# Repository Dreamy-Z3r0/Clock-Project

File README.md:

# Clock project
Final product is a digital wallclock that makes use of an STM32 Blue Pill as main microcontroller and a generic ESP8266 as gateway for remote access.

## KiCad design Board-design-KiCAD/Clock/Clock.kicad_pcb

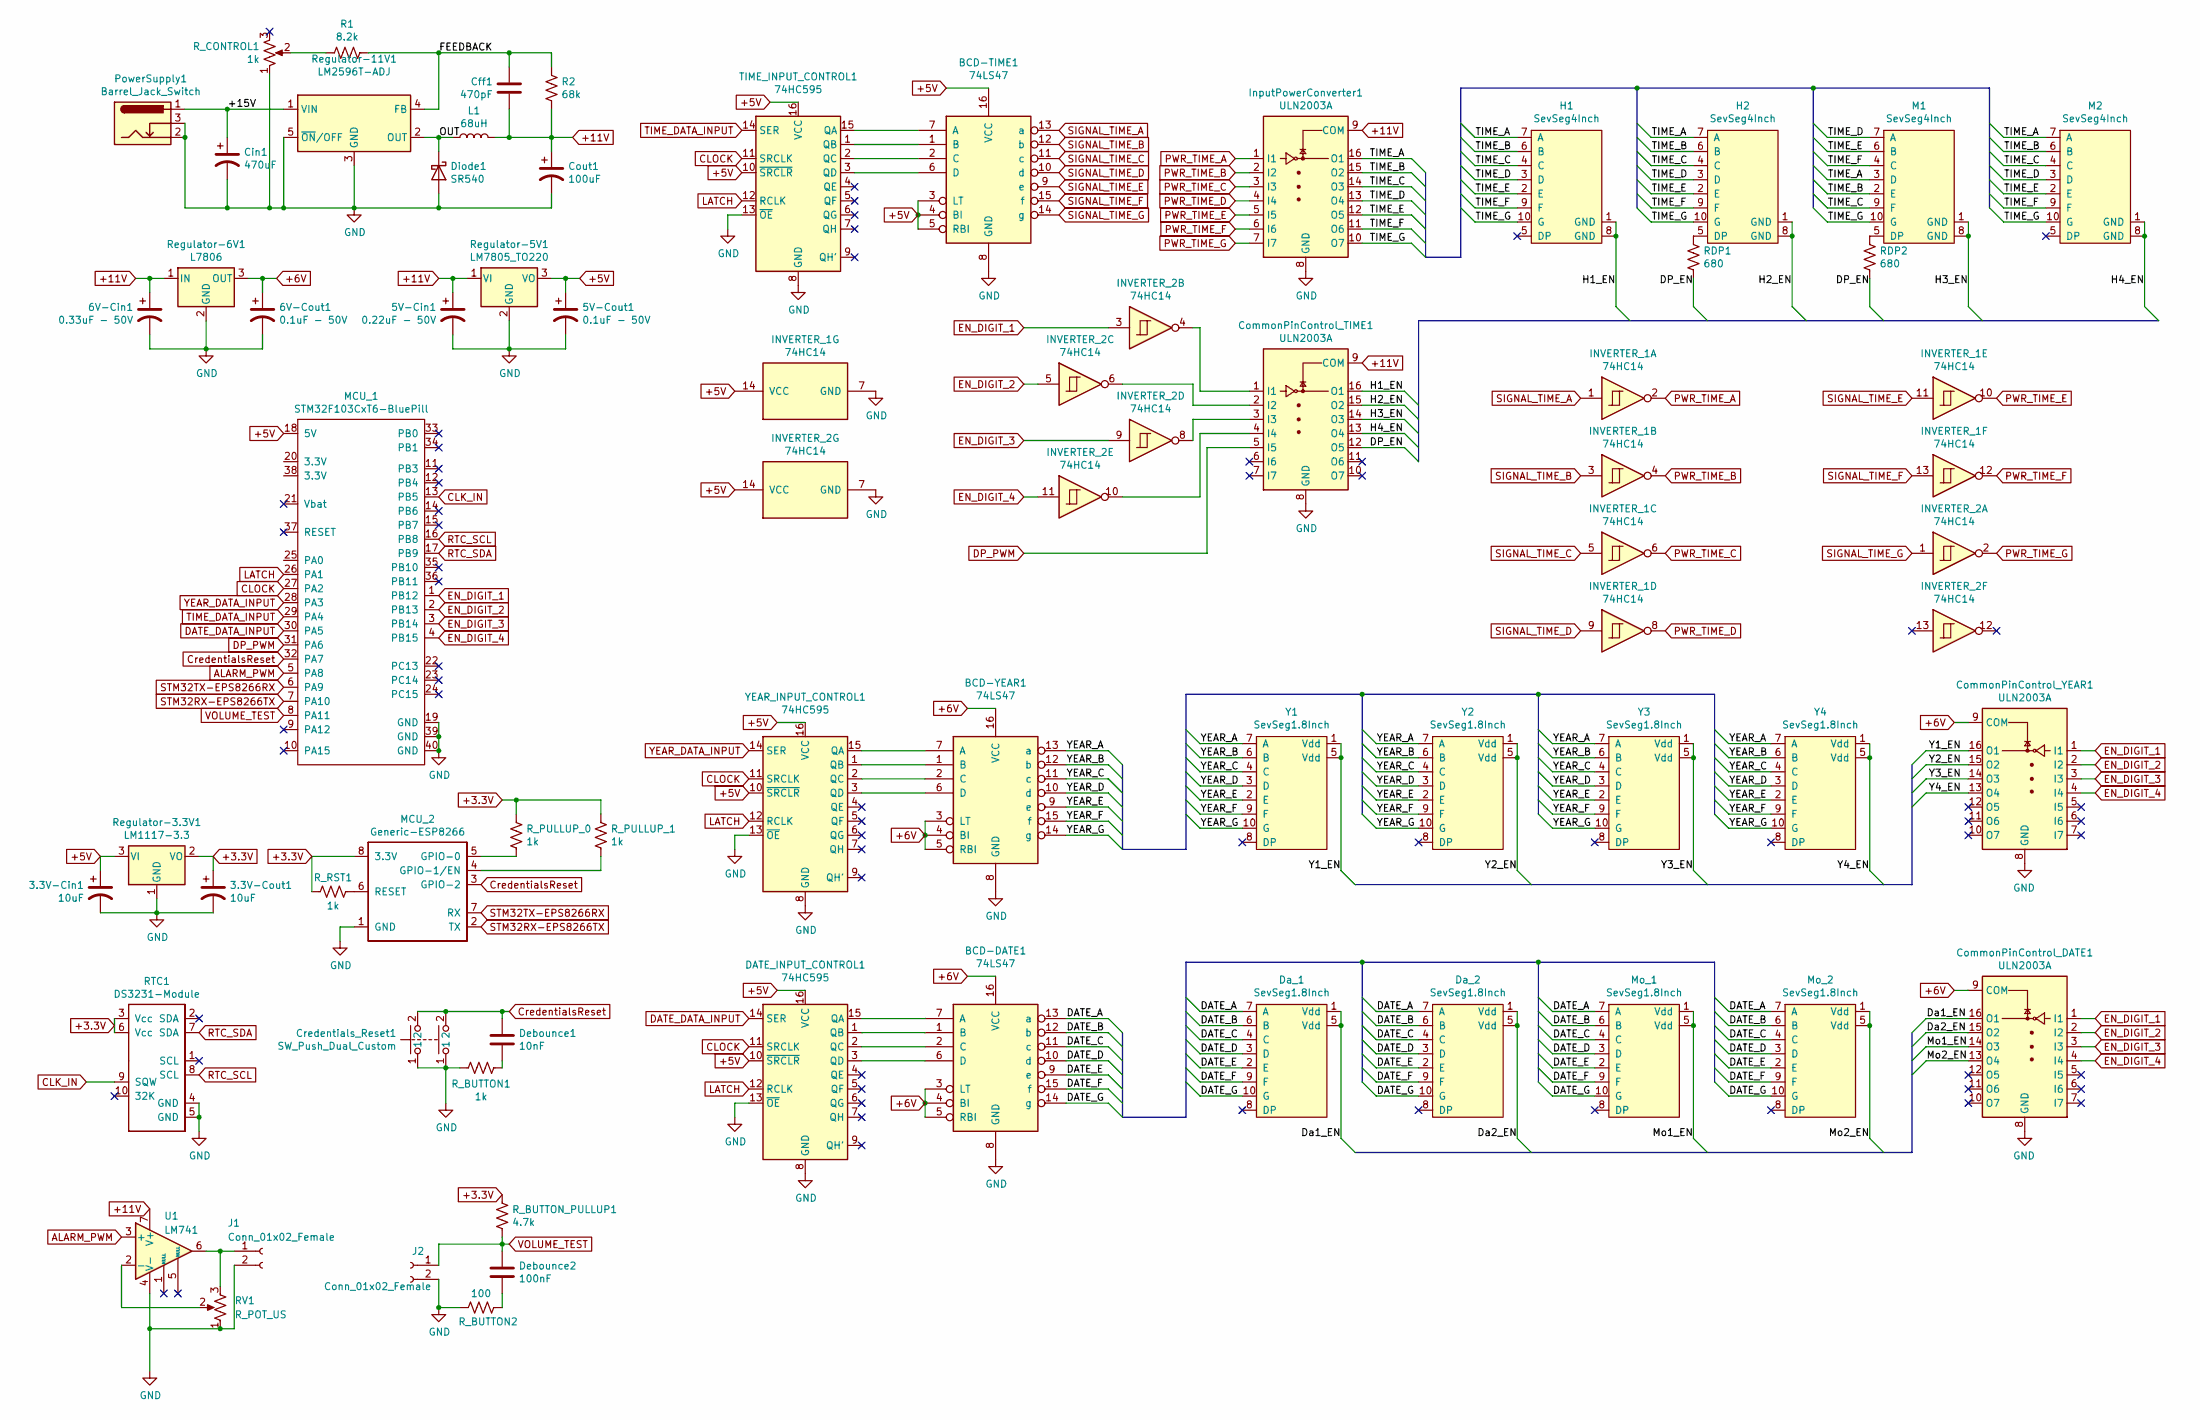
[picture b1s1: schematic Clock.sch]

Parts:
3.3V-Cin1, 3.3V-Cout1: 10uF; CP_Radial_D4.0mm_P2.00mm
5V-Cin1: 0.22uF - 50V; CP_Radial_D4.0mm_P2.00mm
5V-Cout1, 6V-Cout1: 0.1uF - 50V; CP_Radial_D5.0mm_P2.00mm
6V-Cin1: 0.33uF - 50V; CP_Radial_D4.0mm_P2.00mm
BCD-DATE1: 74LS47; DIP-16_W7.62mm_Socket_LongPads
BCD-TIME1: 74LS47; DIP-16_W7.62mm_Socket_LongPads
BCD-YEAR1: 74LS47; DIP-16_W7.62mm_Socket_LongPads
Cff1: 470pF; CP_Radial_H15.0mm_W14.0mm_T8.0mm_P8.5mm_Horizontal
Cin1: 470uF; CP_Radial_D10.0mm_P5.00mm
CommonPinControl_DATE1: ULN2003A; DIP-16_W7.62mm_Socket_LongPads
CommonPinControl_TIME1: ULN2003A; DIP-16_W7.62mm_Socket_LongPads
CommonPinControl_YEAR1: ULN2003A; DIP-16_W7.62mm_Socket_LongPads
Cout1: 100uF; CP_Radial_D8.0mm_P3.50mm
Credentials_Reset1: SW_Push_Dual_Custom; SW_PUSH-12mm_Wuerth-430476085716
DATE_INPUT_CONTROL1: 74HC595; DIP-16_W7.62mm_Socket_LongPads
Da_1, Da_2: SevSeg1.8Inch
Debounce1: 10nF; CP_Radial_H15.0mm_W14.0mm_T8.0mm_P8.5mm_Horizontal
Debounce2: 100nF; CP_Radial_H15.0mm_W14.0mm_T8.0mm_P8.5mm_Horizontal
Diode1: SR540; D_5600_9500Metric
H1, H2: SevSeg4Inch; SevSeg4inch
INVERTER_1, INVERTER_2: 74HC14; DIP-14_W7.62mm_Socket_LongPads
InputPowerConverter1: ULN2003A; DIP-16_W7.62mm_Socket_LongPads
J1, J2: Conn_01x02_Female; PinHeader_1x02_P2.54mm_Vertical
L1: 68uH; L_Radial_D10.0mm_P5.5mm
M1, M2: SevSeg4Inch; SevSeg4inch
MCU_1: STM32F103CxT6-BluePill
MCU_2: Generic-ESP8266
Mo_1, Mo_2: SevSeg1.8Inch
PowerSupply1: Barrel_Jack_Switch; BarrelJack_Horizontal
R1: 8.2k; R_Axial_DIN0207_L6.3mm_D2.5mm_P10.16mm_Horizontal
R2: 68k; R_Axial_DIN0207_L6.3mm_D2.5mm_P10.16mm_Horizontal
RDP1, RDP2: 680; R_Axial_DIN0207_L6.3mm_D2.5mm_P10.16mm_Horizontal
RTC1: DS3231-Module
RV1: R_POT_US; Potentiometer_Piher_T-16H_Single_Horizontal
R_BUTTON1: 1k; R_Axial_DIN0207_L6.3mm_D2.5mm_P10.16mm_Horizontal
R_BUTTON2: 100; R_Axial_DIN0207_L6.3mm_D2.5mm_P10.16mm_Horizontal
R_BUTTON_PULLUP1: 4.7k; R_Axial_DIN0207_L6.3mm_D2.5mm_P10.16mm_Horizontal
R_CONTROL1: 1k; Potentiometer_Vishay_T73YP_Vertical
R_PULLUP_0, R_PULLUP_1: 1k; R_Axial_DIN0207_L6.3mm_D2.5mm_P10.16mm_Horizontal
R_RST1: 1k; R_Axial_DIN0207_L6.3mm_D2.5mm_P10.16mm_Horizontal
Regulator-3.3V1: LM1117-3.3; TO-220-3_Horizontal_TabDown
Regulator-5V1: LM7805_TO220; TO-220-3_Horizontal_TabDown
Regulator-6V1: L7806; TO-220-3_Horizontal_TabDown
Regulator-11V1: LM2596T-ADJ; TO-220-5_Horizontal_TabUp
TIME_INPUT_CONTROL1: 74HC595; DIP-16_W7.62mm_Socket_LongPads
U1: LM741; DIP-8_W7.62mm_Socket_LongPads
Y1, Y2, Y3, Y4: SevSeg1.8Inch
YEAR_INPUT_CONTROL1: 74HC595; DIP-16_W7.62mm_Socket_LongPads

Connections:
+3.3V: 3.3V-Cout1.1, MCU_2.8 (3.3V), RTC1.3 (Vcc), RTC1.6 (Vcc), R_BUTTON_PULLUP1.1, R_PULLUP_0.1, R_PULLUP_1.1, R_RST1.2, Regulator-3.3V1.2 (VO)
+5V: 3.3V-Cin1.1, 5V-Cout1.1, BCD-TIME1.3 (LT), BCD-TIME1.4 (BI), BCD-TIME1.5 (RBI), BCD-TIME1.16 (VCC), DATE_INPUT_CONTROL1.10 (~SRCLR), DATE_INPUT_CONTROL1.16 (VCC), INVERTER_1.14 (VCC), INVERTER_2.14 (VCC), MCU_1.18 (5V), Regulator-3.3V1.3 (VI), Regulator-5V1.3 (VO), TIME_INPUT_CONTROL1.10 (~SRCLR), TIME_INPUT_CONTROL1.16 (VCC), YEAR_INPUT_CONTROL1.10 (~SRCLR), YEAR_INPUT_CONTROL1.16 (VCC)
+6V: 6V-Cout1.1, BCD-DATE1.3 (LT), BCD-DATE1.4 (BI), BCD-DATE1.5 (RBI), BCD-DATE1.16 (VCC), BCD-YEAR1.3 (LT), BCD-YEAR1.4 (BI), BCD-YEAR1.5 (RBI), BCD-YEAR1.16 (VCC), CommonPinControl_DATE1.9 (COM), CommonPinControl_YEAR1.9 (COM), Regulator-6V1.3 (OUT)
+11V: 5V-Cin1.1, 6V-Cin1.1, Cff1.2, CommonPinControl_TIME1.9 (COM), Cout1.1, InputPowerConverter1.9 (COM), L1.2, R2.2, Regulator-5V1.1 (VI), Regulator-6V1.1 (IN), U1.7 (V+)
/+15V: Cin1.1, PowerSupply1.1, Regulator-11V1.1 (VIN)
/DATE_A: BCD-DATE1.13 (a), Da_1.7 (A), Da_2.7 (A), Mo_1.7 (A), Mo_2.7 (A)
/DATE_B: BCD-DATE1.12 (b), Da_1.6 (B), Da_2.6 (B), Mo_1.6 (B), Mo_2.6 (B)
/DATE_C: BCD-DATE1.11 (c), Da_1.4 (C), Da_2.4 (C), Mo_1.4 (C), Mo_2.4 (C)
/DATE_D: BCD-DATE1.10 (d), Da_1.3 (D), Da_2.3 (D), Mo_1.3 (D), Mo_2.3 (D)
/DATE_E: BCD-DATE1.9 (e), Da_1.2 (E), Da_2.2 (E), Mo_1.2 (E), Mo_2.2 (E)
/DATE_F: BCD-DATE1.15 (f), Da_1.9 (F), Da_2.9 (F), Mo_1.9 (F), Mo_2.9 (F)
/DATE_G: BCD-DATE1.14 (g), Da_1.10 (G), Da_2.10 (G), Mo_1.10 (G), Mo_2.10 (G)
/DP_EN: CommonPinControl_TIME1.12 (O5), RDP1.2, RDP2.2
/Da1_EN: CommonPinControl_DATE1.16 (O1), Da_1.1 (Vdd), Da_1.5 (Vdd)
/Da2_EN: CommonPinControl_DATE1.15 (O2), Da_2.1 (Vdd), Da_2.5 (Vdd)
/FEEDBACK: Cff1.1, R1.2, R2.1, Regulator-11V1.4 (FB)
/H1_EN: CommonPinControl_TIME1.16 (O1), H1.1 (GND), H1.8 (GND)
/H2_EN: CommonPinControl_TIME1.15 (O2), H2.1 (GND), H2.8 (GND)
/H3_EN: CommonPinControl_TIME1.14 (O3), M1.1 (GND), M1.8 (GND)
/H4_EN: CommonPinControl_TIME1.13 (O4), M2.1 (GND), M2.8 (GND)
/Mo1_EN: CommonPinControl_DATE1.14 (O3), Mo_1.1 (Vdd), Mo_1.5 (Vdd)
/Mo2_EN: CommonPinControl_DATE1.13 (O4), Mo_2.1 (Vdd), Mo_2.5 (Vdd)
/OUT: Diode1.1 (K), L1.1, Regulator-11V1.2 (OUT)
/TIME_A: H1.7 (A), H2.7 (A), InputPowerConverter1.16 (O1), M1.3 (D), M2.7 (A)
/TIME_B: H1.6 (B), H2.6 (B), InputPowerConverter1.15 (O2), M1.2 (E), M2.6 (B)
/TIME_C: H1.4 (C), H2.4 (C), InputPowerConverter1.14 (O3), M1.9 (F), M2.4 (C)
/TIME_D: H1.3 (D), H2.3 (D), InputPowerConverter1.13 (O4), M1.7 (A), M2.3 (D)
/TIME_E: H1.2 (E), H2.2 (E), InputPowerConverter1.12 (O5), M1.6 (B), M2.2 (E)
/TIME_F: H1.9 (F), H2.9 (F), InputPowerConverter1.11 (O6), M1.4 (C), M2.9 (F)
/TIME_G: H1.10 (G), H2.10 (G), InputPowerConverter1.10 (O7), M1.10 (G), M2.10 (G)
/Y1_EN: CommonPinControl_YEAR1.16 (O1), Y1.1 (Vdd), Y1.5 (Vdd)
/Y2_EN: CommonPinControl_YEAR1.15 (O2), Y2.1 (Vdd), Y2.5 (Vdd)
/Y3_EN: CommonPinControl_YEAR1.14 (O3), Y3.1 (Vdd), Y3.5 (Vdd)
/Y4_EN: CommonPinControl_YEAR1.13 (O4), Y4.1 (Vdd), Y4.5 (Vdd)
/YEAR_A: BCD-YEAR1.13 (a), Y1.7 (A), Y2.7 (A), Y3.7 (A), Y4.7 (A)
/YEAR_B: BCD-YEAR1.12 (b), Y1.6 (B), Y2.6 (B), Y3.6 (B), Y4.6 (B)
/YEAR_C: BCD-YEAR1.11 (c), Y1.4 (C), Y2.4 (C), Y3.4 (C), Y4.4 (C)
/YEAR_D: BCD-YEAR1.10 (d), Y1.3 (D), Y2.3 (D), Y3.3 (D), Y4.3 (D)
/YEAR_E: BCD-YEAR1.9 (e), Y1.2 (E), Y2.2 (E), Y3.2 (E), Y4.2 (E)
/YEAR_F: BCD-YEAR1.15 (f), Y1.9 (F), Y2.9 (F), Y3.9 (F), Y4.9 (F)
/YEAR_G: BCD-YEAR1.14 (g), Y1.10 (G), Y2.10 (G), Y3.10 (G), Y4.10 (G)
ALARM_PWM: MCU_1.5 (PA8), U1.3 (+)
CLK_IN: MCU_1.13 (PB5), RTC1.9 (SQW)
CLOCK: DATE_INPUT_CONTROL1.11 (SRCLK), MCU_1.27 (PA2), TIME_INPUT_CONTROL1.11 (SRCLK), YEAR_INPUT_CONTROL1.11 (SRCLK)
CredentialsReset: Credentials_Reset1.2, Debounce1.1, MCU_1.32 (PA7), MCU_2.3 (GPIO-2)
DATE_DATA_INPUT: DATE_INPUT_CONTROL1.14 (SER), MCU_1.30 (PA5)
DP_PWM: CommonPinControl_TIME1.5 (I5), MCU_1.31 (PA6)
EN_DIGIT_1: CommonPinControl_DATE1.1 (I1), CommonPinControl_YEAR1.1 (I1), INVERTER_2.3, MCU_1.1 (PB12)
EN_DIGIT_2: CommonPinControl_DATE1.2 (I2), CommonPinControl_YEAR1.2 (I2), INVERTER_2.5, MCU_1.2 (PB13)
EN_DIGIT_3: CommonPinControl_DATE1.3 (I3), CommonPinControl_YEAR1.3 (I3), INVERTER_2.9, MCU_1.3 (PB14)
EN_DIGIT_4: CommonPinControl_DATE1.4 (I4), CommonPinControl_YEAR1.4 (I4), INVERTER_2.11, MCU_1.4 (PB15)
GND: 3.3V-Cin1.2, 3.3V-Cout1.2, 5V-Cin1.2, 5V-Cout1.2, 6V-Cin1.2, 6V-Cout1.2, BCD-DATE1.8 (GND), BCD-TIME1.8 (GND), BCD-YEAR1.8 (GND), Cin1.2, CommonPinControl_DATE1.8 (GND), CommonPinControl_TIME1.8 (GND), CommonPinControl_YEAR1.8 (GND), Cout1.2, Credentials_Reset1.1, DATE_INPUT_CONTROL1.8 (GND), DATE_INPUT_CONTROL1.13 (~OE), Diode1.2 (A), INVERTER_1.7 (GND), INVERTER_2.7 (GND), InputPowerConverter1.8 (GND), J1.2, J2.2, MCU_1.19 (GND), MCU_1.39 (GND), MCU_1.40 (GND), MCU_2.1 (GND), PowerSupply1.2, PowerSupply1.3, RTC1.4 (GND), RTC1.5 (GND), RV1.1, R_BUTTON1.1, R_BUTTON2.2, R_CONTROL1.1, Regulator-3.3V1.1 (GND), Regulator-5V1.2 (GND), Regulator-6V1.2 (GND), Regulator-11V1.3 (GND), Regulator-11V1.5 (~ON~/OFF), TIME_INPUT_CONTROL1.8 (GND), TIME_INPUT_CONTROL1.13 (~OE), U1.4 (V-), YEAR_INPUT_CONTROL1.8 (GND), YEAR_INPUT_CONTROL1.13 (~OE)
LATCH: DATE_INPUT_CONTROL1.12 (RCLK), MCU_1.26 (PA1), TIME_INPUT_CONTROL1.12 (RCLK), YEAR_INPUT_CONTROL1.12 (RCLK)
unnamed: BCD-DATE1.1 (B), DATE_INPUT_CONTROL1.1 (QB)
unnamed: BCD-DATE1.2 (C), DATE_INPUT_CONTROL1.2 (QC)
unnamed: BCD-DATE1.6 (D), DATE_INPUT_CONTROL1.3 (QD)
unnamed: BCD-DATE1.7 (A), DATE_INPUT_CONTROL1.15 (QA)
unnamed: BCD-TIME1.1 (B), TIME_INPUT_CONTROL1.1 (QB)
unnamed: BCD-TIME1.2 (C), TIME_INPUT_CONTROL1.2 (QC)
unnamed: BCD-TIME1.6 (D), TIME_INPUT_CONTROL1.3 (QD)
unnamed: BCD-TIME1.7 (A), TIME_INPUT_CONTROL1.15 (QA)
unnamed: BCD-YEAR1.1 (B), YEAR_INPUT_CONTROL1.1 (QB)
unnamed: BCD-YEAR1.2 (C), YEAR_INPUT_CONTROL1.2 (QC)
unnamed: BCD-YEAR1.6 (D), YEAR_INPUT_CONTROL1.3 (QD)
unnamed: BCD-YEAR1.7 (A), YEAR_INPUT_CONTROL1.15 (QA)
unnamed: CommonPinControl_TIME1.1 (I1), INVERTER_2.4
unnamed: CommonPinControl_TIME1.2 (I2), INVERTER_2.6
unnamed: CommonPinControl_TIME1.3 (I3), INVERTER_2.8
unnamed: CommonPinControl_TIME1.4 (I4), INVERTER_2.10
unnamed: Debounce1.2, R_BUTTON1.2
unnamed: Debounce2.2, R_BUTTON2.1
unnamed: H2.5 (DP), RDP1.1
unnamed: J1.1, RV1.3, U1.6
unnamed: M1.5 (DP), RDP2.1
unnamed: MCU_2.4 (GPIO-1/EN), R_PULLUP_1.2
unnamed: MCU_2.5 (GPIO-0), R_PULLUP_0.2
unnamed: MCU_2.6 (RESET), R_RST1.1
unnamed: R1.1, R_CONTROL1.2
unnamed: RV1.2, U1.2 (-)
PWR_TIME_A: INVERTER_1.2, InputPowerConverter1.1 (I1)
PWR_TIME_B: INVERTER_1.4, InputPowerConverter1.2 (I2)
PWR_TIME_C: INVERTER_1.6, InputPowerConverter1.3 (I3)
PWR_TIME_D: INVERTER_1.8, InputPowerConverter1.4 (I4)
PWR_TIME_E: INVERTER_1.10, InputPowerConverter1.5 (I5)
PWR_TIME_F: INVERTER_1.12, InputPowerConverter1.6 (I6)
PWR_TIME_G: INVERTER_2.2, InputPowerConverter1.7 (I7)
RTC_SCL: MCU_1.16 (PB8), RTC1.8 (SCL)
RTC_SDA: MCU_1.17 (PB9), RTC1.7 (SDA)
SIGNAL_TIME_A: BCD-TIME1.13 (a), INVERTER_1.1
SIGNAL_TIME_B: BCD-TIME1.12 (b), INVERTER_1.3
SIGNAL_TIME_C: BCD-TIME1.11 (c), INVERTER_1.5
SIGNAL_TIME_D: BCD-TIME1.10 (d), INVERTER_1.9
SIGNAL_TIME_E: BCD-TIME1.9 (e), INVERTER_1.11
SIGNAL_TIME_F: BCD-TIME1.15 (f), INVERTER_1.13
SIGNAL_TIME_G: BCD-TIME1.14 (g), INVERTER_2.1
STM32RX-EPS8266TX: MCU_1.7 (PA10), MCU_2.2 (TX)
STM32TX-EPS8266RX: MCU_1.6 (PA9), MCU_2.7 (RX)
TIME_DATA_INPUT: MCU_1.29 (PA4), TIME_INPUT_CONTROL1.14 (SER)
VOLUME_TEST: Debounce2.1, J2.1, MCU_1.8 (PA11), R_BUTTON_PULLUP1.2
YEAR_DATA_INPUT: MCU_1.28 (PA3), YEAR_INPUT_CONTROL1.14 (SER)

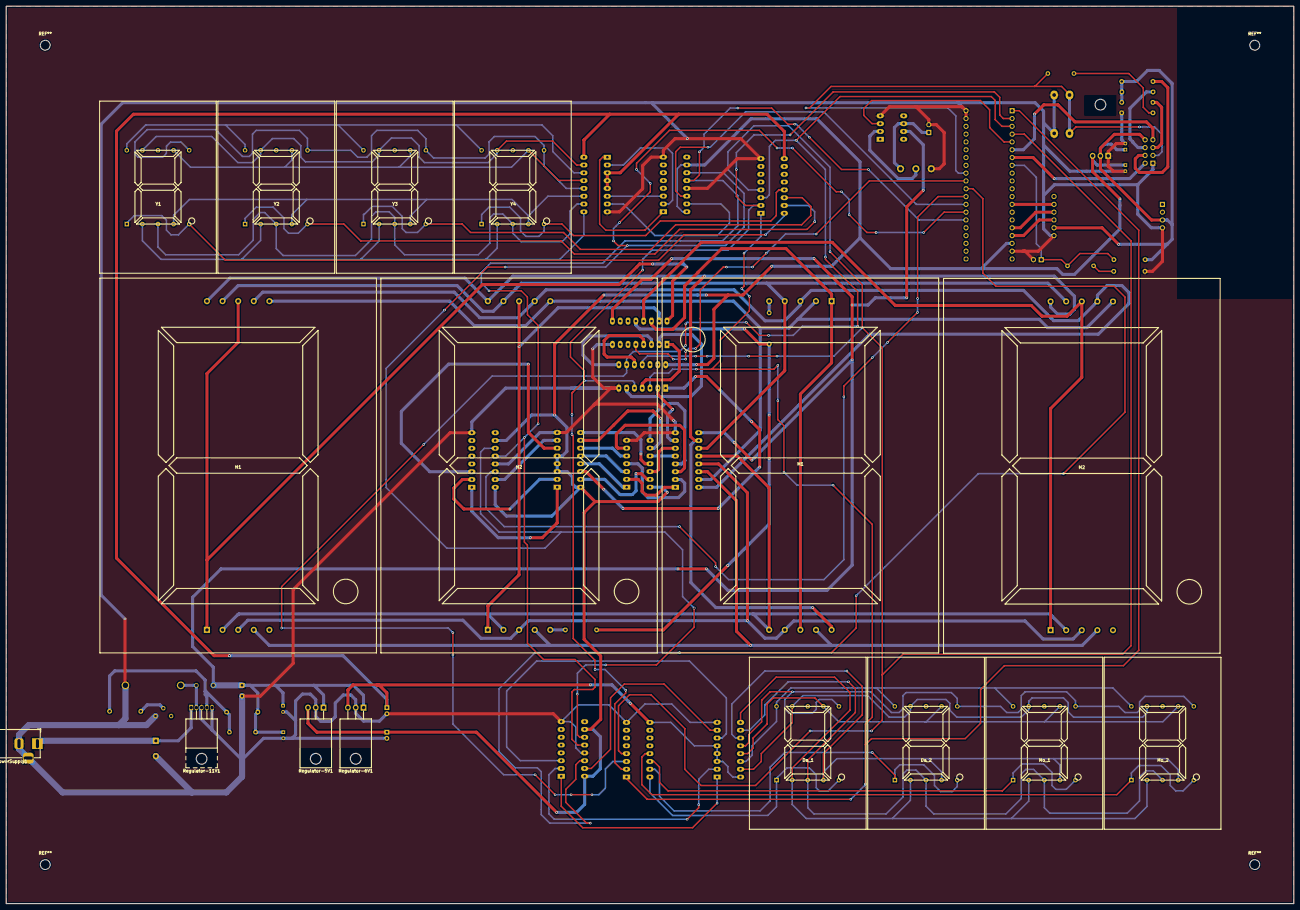
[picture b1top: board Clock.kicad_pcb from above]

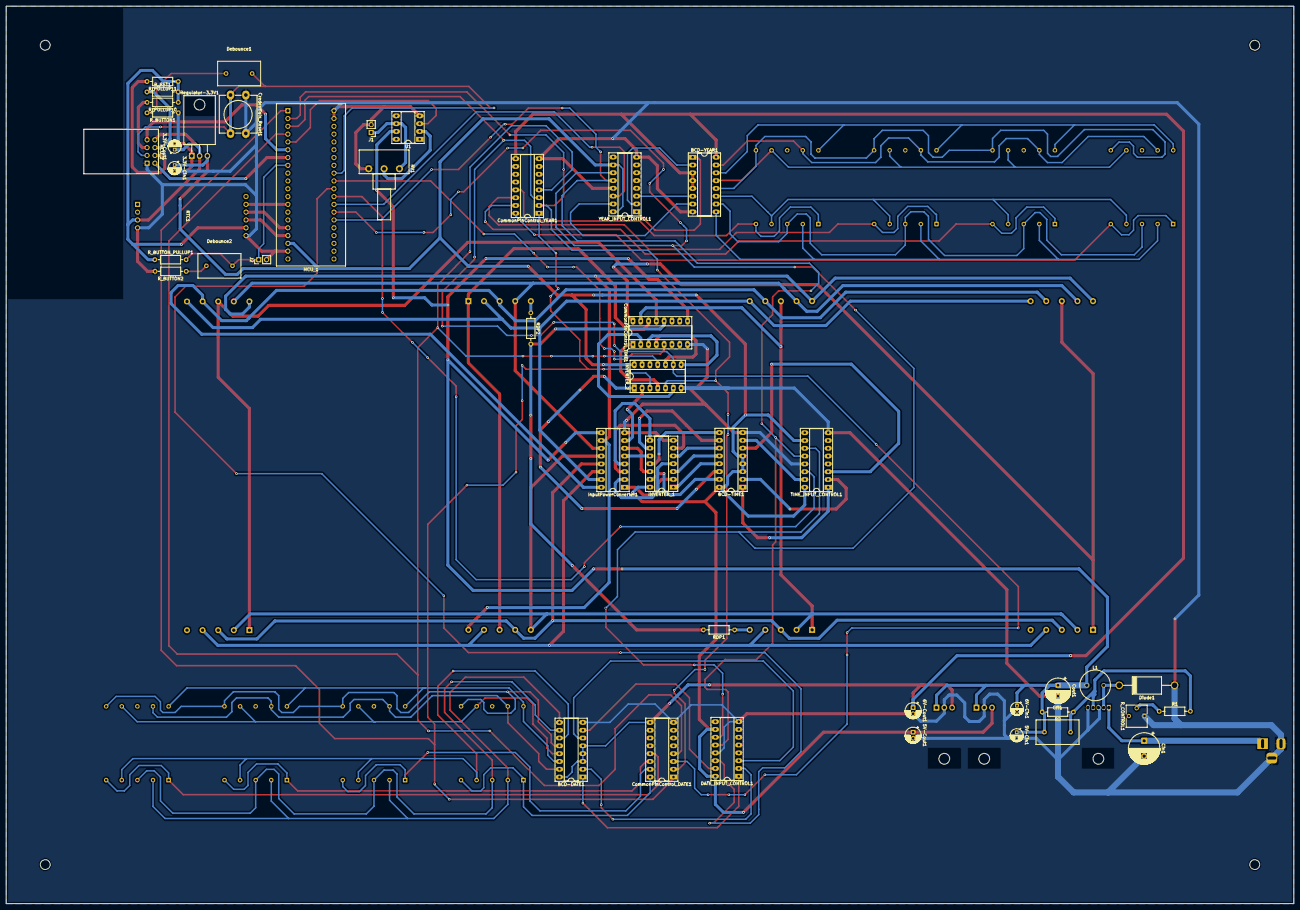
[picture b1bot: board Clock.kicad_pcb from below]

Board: 2 copper layers, 419.1 x 292.1 mm, 61 parts (45 on the bottom side), 100 nets.

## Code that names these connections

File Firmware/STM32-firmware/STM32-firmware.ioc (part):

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PB13.GPIOParameters=GPIO_Speed,GPIO_Label
Mcu.UserName=STM32F103CBTx
PB14.GPIO_Label=EN_DIGIT_3
PC13-TAMPER-RTC.GPIOParameters=GPIO_Label
PA2.GPIO_Speed=GPIO_SPEED_FREQ_HIGH
PA11.GPIOParameters=GPIO_PuPd,GPIO_Label,GPIO_ModeDefaultEXTI
PA3.GPIOParameters=GPIO_Speed,GPIO_Label
PA6.GPIO_Label=DP_OUT
PA11.GPIO_PuPd=GPIO_PULLUP
PB13.GPIO_Label=EN_DIGIT_2
PA3.GPIO_Speed=GPIO_SPEED_FREQ_HIGH
PB13.Signal=GPIO_Output
PB15.Signal=GPIO_Output
PA2.GPIOParameters=GPIO_Speed,GPIO_Label
RCC.SYSCLKSource=RCC_SYSCLKSOURCE_PLLCLK
PB5.GPIOParameters=GPIO_Label,GPIO_ModeDefaultEXTI
PD1-OSC_OUT.Signal=RCC_OSC_OUT
PA8.GPIOParameters=GPIO_Label
PA4.GPIO_Speed=GPIO_SPEED_FREQ_HIGH
PB12.GPIO_Label=EN_DIGIT_1
PA1.GPIOParameters=GPIO_Speed,PinState,GPIO_Label
PA14.Mode=Serial_Wire
PA8.Signal=GPIO_Output
PB9.Signal=I2C1_SDA
Mcu.Package=LQFP48
PA6.Signal=GPIO_Output
PA2.GPIO_Label=CLOCK
PA10.Signal=USART1_RX
PA5.GPIOParameters=GPIO_Speed,GPIO_Label
PA1.PinState=GPIO_PIN_RESET
PB14.GPIOParameters=GPIO_Speed,GPIO_Label
PB5.GPIO_Label=CLK_IN
PA4.GPIO_Label=TIME
PA3.Signal=GPIO_Output
PB5.GPIO_ModeDefaultEXTI=GPIO_MODE_IT_RISING
PA6.GPIOParameters=GPIO_Label
PD1-OSC_OUT.Mode=HSE-External-Oscillator
PA10.Mode=Asynchronous
PA7.GPIO_ModeDefaultEXTI=GPIO_MODE_IT_FALLING
PC13-TAMPER-RTC.Signal=GPIO_Output
PA11.GPIO_Label=VOLUME_TEST
PD0-OSC_IN.Signal=RCC_OSC_IN
PA13.Signal=SYS_JTMS-SWDIO
PA9.Mode=Asynchronous
PA8.GPIO_Label=ALARM_PWM
PB14.GPIO_Speed=GPIO_SPEED_FREQ_HIGH
PB9.Mode=I2C
PA9.Signal=USART1_TX
PB13.GPIO_Speed=GPIO_SPEED_FREQ_HIGH
PA1.Signal=GPIO_Output
PB12.GPIO_Speed=GPIO_SPEED_FREQ_HIGH
PD0-OSC_IN.Mode=HSE-External-Oscillator
PB14.Signal=GPIO_Output
PA5.Signal=GPIO_Output
board=custom
PC13-TAMPER-RTC.GPIO_Label=BUILTIN_LED
PB15.GPIO_Label=EN_DIGIT_4
PB15.GPIO_Speed=GPIO_SPEED_FREQ_HIGH
PA1.GPIO_Speed=GPIO_SPEED_FREQ_HIGH
PA1.GPIO_Label=LATCH
PA4.GPIOParameters=GPIO_Speed,GPIO_Label
PB15.GPIOParameters=GPIO_Speed,GPIO_Label
PA13.Mode=Serial_Wire
Mcu.Name=STM32F103C(8-B)Tx
PA2.Signal=GPIO_Output
PA4.Signal=GPIO_Output
RCC.SYSCLKFreq_VALUE=72000000
PB5.Signal=GPXTI5
PA7.GPIO_Label=ESP8266_RESET
PA5.GPIO_Label=DATE
PA11.Signal=GPXTI11
PA14.Signal=SYS_JTCK-SWCLK
PA5.GPIO_Speed=GPIO_SPEED_FREQ_HIGH
PB8.Mode=I2C
PB8.Signal=I2C1_SCL
PA11.GPIO_ModeDefaultEXTI=GPIO_MODE_IT_FALLING
PA7.GPIOParameters=GPIO_Label,GPIO_ModeDefaultEXTI
PB12.GPIOParameters=GPIO_Speed,GPIO_Label
PB12.Signal=GPIO_Output
PA3.GPIO_Label=YEAR
PA7.Signal=GPXTI7

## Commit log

2020-09-05 add README.md
2020-09-05 add ESP8266 firmware
2020-09-05 add general info for ESP8266 firmware
2020-09-05 add rubbish
2020-09-05 undo the rubbish
2020-09-05 fix ssid line
2020-09-10 Rearrange repositories
2020-09-10 Rearrange some components on the schematics
2020-09-14 Create project for STM32 firmware and add some general settings
2020-09-14 Add some output signals
2020-09-14 Add new variables and functional commands
2020-09-14 Add user-defined function content
2020-09-16 Add RTC functionalities
2020-09-16 Add some components
2020-09-16 Add power supply and 11-V regulator
2020-09-16 Nada
2020-09-16 Cache auto update
2020-09-17 Build PCB part for external power supply
2020-09-17 Add some PCB routes
2020-09-18 Add new tracks
2020-09-19 Add some display wirings
2020-09-19 Finish display wirings
2020-09-19 Rearrange some minor components
2020-09-19 Create new symbol and footprint for STM32F103CxT6 Blue Pill
2020-09-19 Add Blue Pill to schematics
2020-09-19 Add Blue Pill footprint on PCB design and perform existing wirings
2020-09-19 Finish integrating WiFi and RTC
2020-09-19 Not much changed
2020-09-20 Add I2C settings to STM32 firmware
2020-09-20 Update part(s): DS3231 RTC Module
2020-09-22 Add and allow access to ESP8266 local server
2020-09-23 Remove Station (STA) mode; Allow setting up AP credentials; Put HTML page contents to a separate file.
2020-09-23 Remove some debugging lines
2020-09-25 Add extra methods handling inputs from HTML page
2020-09-26 Add time and date input for HTML index
2020-09-26 Add processing functions for date and time input from HTML; Add data transfer function via UART.
2020-09-26 Remove abundant parameters.
2020-09-27 Add credential reset button for ESP8266
2020-09-27 Discard STM32 firmware for rework
2020-09-27 STM32 cleared
2020-09-27 Add credential reset, hardware setup needed
2020-09-28 Modify button circuit and build code for button management.
2020-09-28 Update fp-info-cache
2020-09-28 Add DS3231 memory write
2020-09-29 Add timer functionalities
2020-09-30 Add functions handling UART3; Add some code comments.
2020-09-30 Update some variable names
2020-09-30 Rework on UART transfer
2020-10-01 Remove DMA for UART3 and UART1 TX
2020-10-02 New changes to overcome runtime errors
2020-10-02 Update CubeMX project according to the source code
2020-10-05 Add management flags and flag functionalities in while(1) loop.
2020-10-05 Fix some errors in calculations for PWM on channel 3
2020-10-06 Use I2C on alternative pins. Code finished.
2020-10-07 Add some names
2020-10-09 Possible solution for audio amplifier
2020-10-16 Fix some existing errors
2020-10-16 More
2020-10-25 Rework on alarm function
2020-10-28 Finish up PCB design and fix some minor firmware issue
2020-10-29 Add mounting holes and generate gerber files
2020-10-31 Rearrange some parts of the main.c, no change in general
2020-11-13 Resolve problems raised from datasheets
2020-11-13 Place origin
2020-11-13 Export gerber files to meet manufacturer's requirements
